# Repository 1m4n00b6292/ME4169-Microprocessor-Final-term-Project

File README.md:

# ME4169 Microprocessor Final term project

This is the final term project of ME4169 - Microprocessor course conducted by HUST

## Overview

**ME4169 Microprocessor Final term project**, aka, **VIXULY** is a closed-loop DC motor speed controller built around an **ATmega88PA** running at 16 MHz. The motor speed is measured by a quadrature encoder and regulated by a fixed-point PID controller. The target speed can be set either by a **potentiometer** or by commands sent over **UART**. A small **WeAct ST7735 TFT module** shows the current mode, the system state, the target speed and the measured speed (RPM).

The firmware is written as bare-metal AVR code (direct register access, hand-written ISRs). The Arduino framework is only used for `millis()` and the `setup()`/`loop()` entry points, under PlatformIO.

<!-- Fixed width, centered -->
<p align="center">
  
  <br>
  <em>Figure 1: PCB 3D view (top)</em>
</p>

## Main Components

### Hardware

| Part | Function |
|------|----------|
| ATmega88PA-A (TQFP-32) + 16 MHz crystal | Main MCU |
| DRV8220 | Brushed DC motor driver (H-bridge) |
| Quadrature encoder | Speed feedback (x4 decoding) |
| [WeAct ST7735 TFT module](https://github.com/WeActStudio/WeAct-ST7735) (128x160) | Status display, SPI |
| TXB0106 | Level shifter between the 5 V MCU and the 3.3 V TFT |
| Potentiometer (RV1) | Manual speed setpoint |
| 2 push buttons + 2 LEDs | RUN / STOP user interface |
| LMR51420 buck + AP2112K-3.3 LDO | 12 V input to 5 V and 3.3 V rails |
| PFET + Zener input stage | Reverse polarity protection |
### Pin Map

| Signal | Pin | Notes |
|--------|-----|-------|
| TFT RST / BL / CS | PB0 / PB1 / PB2 | |
| TFT MOSI / SCK | PB3 / PB5 | Hardware SPI |
| TFT DC | PD7 | |
| Encoder A / B | PD2 / PD3 | INT0 / INT1 |
| Motor nSLEEP | PD4 | |
| Motor IN1/PH, IN2/EN | PD5 / PD6 | Software PWM on Timer2 |
| UART RX | PD0 | RX only |
| Potentiometer | PC0 | ADC0 |
| RUN button / RUN LED | PC1 / PC2 | |
| STOP button / STOP LED | PC3 / PC4 | |

> **JP1** on the board selects the DRV8220 control mode. Keep it **open** for PWM (IN1/IN2) mode (default). If it is soldered, enable `MOTOR_MODE_PH_EN` in `config.h`.

<!-- Fixed width, centered -->
<p align="center">
  
  <br>
  <em>Figure 2: Layout view (top)</em>
</p>

### Software Modules

| File | Description |
|------|-------------|
| `main.cpp` | Entry point: only calls `app_init()` and `app_update()` |
| `app.cpp / app.h` | Application layer: state machine, mode selection, LEDs, display updates (implements `VIXULY_Logic.txt`) |
| `config.h` | **Single place for every tunable value**: pins, TFT, ADC, encoder, motor, PID gains, button timing, UI layout |
| `motion.c / motion.h` | Fixed-point (Q8) PID velocity controller with feed-forward, setpoint ramp, anti-windup and filtered D-term |
| `motor.c / motor.h` | DRV8220 driver, software PWM on Timer2 ISRs (Timer0 / `millis()` untouched) |
| `encoder_mini.cpp / .h` | x4 quadrature decoder, optional STM32-style digital input filter (Timer1), velocity and RPM calculation |
| `button.c / button.h` | Debounced button with short-press / long-press detection |
| `uart.c / uart.h` | Interrupt-driven UART receiver with ring buffer and ASCII integer parser |
| `adc.c / adc.h` | Minimal 10-bit ADC driver |
| `st7735_mini.c / .h` | Lightweight text-only driver for the WeAct ST7735 module (small flash footprint) |

## Operation Logic

The system has three user-visible states: **STOP**, **RUN** and **SELECT** (mode selection). There are two operation modes:

- **POTENTIOMETER**: the speed setpoint comes from the pot on PC0
- **UART**: the speed setpoint comes from serial commands

| Button | Current state | Action | Result |
|--------|---------------|--------|--------|
| STOP | any | Press | Stop the system. The motor driver is put to sleep (PD4 low), the PID is reset, and any unfinished mode selection is cancelled |
| RUN | STOP | Short press | Start running in the current mode |
| RUN | STOP | Hold ~2 s | Enter mode selection |
| RUN | SELECT | Short press | Swap between POTENTIOMETER and UART |
| RUN | SELECT | Hold ~2 s | Confirm the shown mode and return to STOP |
| RUN | RUN | any | Ignored |

**LEDs**

- RUN LED (PC2) is on only while the system is running
- STOP LED (PC4) is on while stopped or selecting

The global variable `running` is `1` while the system is running and `0` otherwise.

## Quick User Guide

### 1. Build and flash

The project uses [PlatformIO](https://platformio.org/).

1. Clone the repository:
   ```bash
   git clone https://github.com/1m4n00b6292/VIXULY-Source-code.git
   ```
2. Open the `Department of Software Engineering` folder in VS Code with the PlatformIO extension.
3. Review `src/config.h`, especially the items in the **Configuration** section below.
4. Build and upload with your ISP programmer, using the debug/programming header on the board.

### 2. Power up

1. Connect a **12 V DC** supply to the input terminal (observe polarity).
2. Connect the motor and the encoder.
3. After power-up the system starts in **STOP** (red "STOP" on the screen, STOP LED on).

### 3. Select a mode

1. In STOP, hold the **RUN** button for about 2 s. The screen shows **SELECT** in orange.
2. Short-press **RUN** to toggle between `Mode: Potentiometer` and `Mode: UART`.
3. Hold **RUN** for about 2 s again to confirm. The system returns to STOP with the chosen mode.

### 4. Run

Short-press **RUN**. The screen shows green **RUNNING**, and the RUN LED turns on.

- **Potentiometer mode**: turn the pot. The center position (with a small dead band) is 0 RPM. Turning it to one side gives clockwise rotation, and turning it to the other side gives counter-clockwise rotation. Full travel corresponds to `APP_MAX_RPM`.
- **UART mode**: send speed commands as described below.

Press **STOP** at any time to stop the motor.

### 5. UART protocol

| Setting | Value |
|---------|-------|
| Baud rate | 115200 |
| Format | 8N1 |
| Direction | RX only (PC to board) |

Send one **signed integer per line**, ending with `\n` or `\r`. The value is clamped to **-255 ... +255** and scaled linearly to **-APP_MAX_RPM ... +APP_MAX_RPM**. Other characters are ignored.

```text
255\n     -> full speed, forward
-128\n    -> about half speed, reverse
0\n       -> stop (motor held at 0 RPM)
```

Example with Python:

```python
import serial
ser = serial.Serial("COM3", 115200)
ser.write(b"200\n")
```

### 6. Display

```text
Mode: Potentiometer        <- active mode
Velocity =                 <- measured speed
 1234 (RPM)
Target = 1500              <- setpoint
RUNNING                    <- state
```

## Configuration

All the important parameters are in `config.h`:

| Parameter | Meaning |
|-----------|---------|
| `ENC_PPR` | **Set this to your encoder's pulses per revolution.** The RPM calculation depends on it |
| `ENC_INVERT` | Swap the encoder counting direction |
| `ENC_FILTER_N`, `ENC_FILTER_SAMPLE_HZ` | Encoder input noise filter (set `ENC_FILTER_N` to 1 to disable) |
| `MOTOR_INVERT` | Flip the motor rotation direction |
| `MOTOR_T2_PRESCALER` | Software PWM frequency (default 32 gives about 1.95 kHz) |
| `MOTION_KP`, `MOTION_KI`, `MOTION_KD`, `MOTION_KFF` | PID and feed-forward gains, **tune these on your motor** |
| `MOTION_ACCEL` | Setpoint ramp rate in units/s (0 = off) |
| `APP_MAX_RPM` | Speed at full pot travel or UART ±255 |
| `APP_OPEN_LOOP` | `1` = send the target directly as PWM duty (no PID), useful for testing the hardware |
| `APP_POT_INVERT`, `APP_POT_DEADBAND` | Potentiometer direction and dead band |
| `BTN_LONG_MS`, `BTN_DEBOUNCE_MS` | Button timing |
| `TFT_LANDSCAPE`, `TFT_COL_OFFSET`, `TFT_ROW_OFFSET` | Display orientation and offsets |

> **Tip:** if something does not behave as expected during bring-up, set `APP_OPEN_LOOP` to `1` first to check the motor and the pot without the PID in the way, then switch back to closed-loop and tune the gains.

## Repository Structure

The repository is organized like a university, with one "department" per area of the project:

```text
VIXULY-Source-code/
├── Department of Administration Services/     # Administration: final term report
│   └── (final term report)
│
├── Department of Electrical Engineering/      # Electrical: PCB design files
│   ├── Docs/                                  #   Datasheets, Reference designs,... used in this project
│   ├── Util/                                  #   External libraries, 3D CAD files used in the PCB design
│   └── 中国制造的PCB/                          #   PCB project, Schematic, Layout, Gerber files,..
│
├── Department of Mechanical Engineering/      # Mechanical: 3D printed parts
│   └── Encoder flange/                        #   Flange with a radial magnet at the center,
│                                              #   for a second encoder used to cross-check
│                                              #   the velocity measurement
│
├── Department of Software Engineering/        # Software: the firmware
│   ├── src/
│   │   ├── main.cpp
│   │   ├── app.cpp / app.h
│   │   ├── config.h
│   │   ├── motion.c / motion.h
│   │   ├── motor.c / motor.h
│   │   ├── encoder_mini.cpp / encoder_mini.h
│   │   ├── button.c / button.h
│   │   ├── uart.c / uart.h
│   │   ├── adc.c / adc.h
│   │   └── st7735_mini.c / st7735_mini.h
│   ├── VIXULY_Logic.txt                       #   Button / mode logic specification
│   └── platformio.ini
│
└── README.md
```

| Folder | Contents |
|--------|----------|
| **Department of Administration Services** | Final term report |
| **Department of Electrical Engineering** | Schematic, PCB files and Gerber files of the VI XU LY board |
| **Department of Mechanical Engineering** | 3D printed parts. Currently a flange with a radial magnet at its center, used for a second encoder that confirms the velocity measurement |
| **Department of Software Engineering** | Firmware for the ATmega88PA (this is what the sections above describe) |

> **Build note:** open the `Department of Software Engineering` folder (not the repo root) in PlatformIO.
## Acknowledgements

- Display module: [WeAct Studio ST7735](https://github.com/WeActStudio/WeAct-ST7735). `st7735_mini` is a trimmed, text-only driver written for this project so that it fits in the ATmega88PA's flash.

## Course Information

- **Course:** ME4169 - Microprocessor
- **University:** Hanoi University of Science and Technology (HUST)
- **Type:** Final term project

## Authors

| Member | GitHub | Role |
|--------|--------|------|
| **1m4n00b** | [@1m4n00b6292](https://github.com/1m4n00b6292) | Hardware and system design: PCB design, schematic, component selection, planning the system function and logic |
| **depzaineversai** | [@anhkiethp58-hue](https://github.com/anhkiethp58-hue) | Firmware: firmware development and integration |

## License

This project is licensed under the [MIT License](LICENSE).

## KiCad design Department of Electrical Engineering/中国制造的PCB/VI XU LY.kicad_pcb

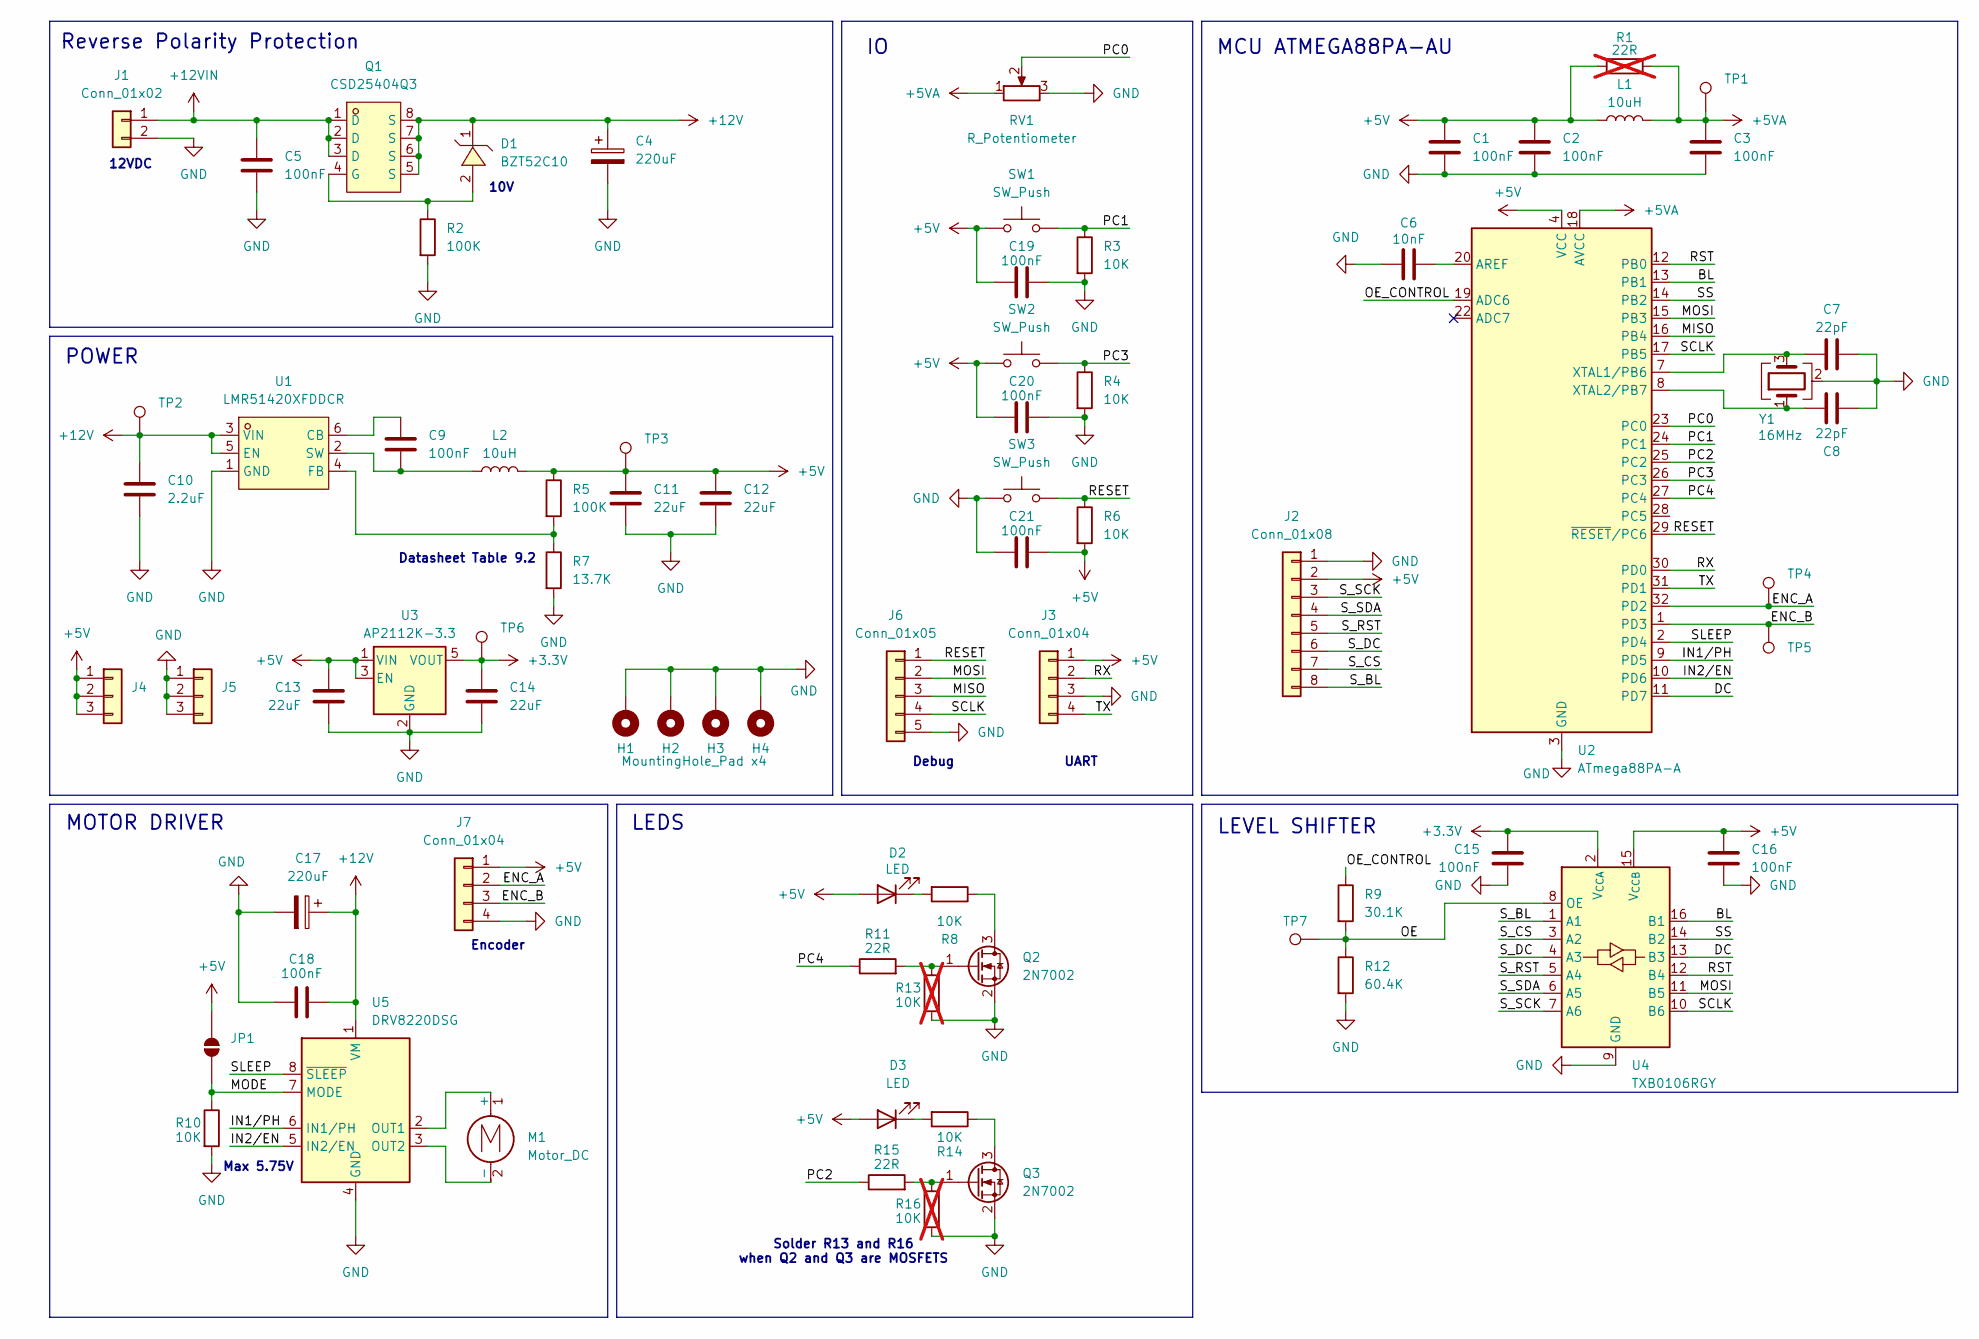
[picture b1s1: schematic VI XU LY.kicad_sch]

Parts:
C1, C2, C3, C9, C15, C16, C18, C19, C20, C21: 100nF; C_0603_1608Metric_Pad1.08x0.95mm_HandSolder
C4, C17: 220uF; CP_Elec_6.3x7.7
C5: 100nF; C_0805_2012Metric_Pad1.18x1.45mm_HandSolder
C6: 10nF; C_0603_1608Metric_Pad1.08x0.95mm_HandSolder
C7, C8: 22pF; C_0603_1608Metric_Pad1.08x0.95mm_HandSolder
C10: 2.2uF; C_0603_1608Metric_Pad1.08x0.95mm_HandSolder
C11, C12, C13, C14: 22uF; C_1206_3216Metric_Pad1.33x1.80mm_HandSolder
D1: BZT52C10; SOD-123_L2.8-W1.8-LS3.7-RD; MPN BZT52C10; LCSC Part C173431
D2, D3: LED; LED_1206_3216Metric_Pad1.42x1.75mm_HandSolder
H1, H2, H3: MountingHole_Pad; MountingHole_3.2mm_M3_Pad_TopBottom
H4: MountingHole_Pad x4; MountingHole_3.2mm_M3_Pad_TopBottom
J1: Conn_01x02; TerminalBlock_Phoenix_MKDS-1,5-2-5.08_1x02_P5.08mm_Horizont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
J2: Conn_01x08; PinSocket_1x08_P2.54mm_Vertical
J3, J7: Conn_01x04; JST_XH_S4B-XH-A-1_1x04_P2.50mm_Horizontal
J4, J5: Conn_01x03; PinHeader_1x03_P2.54mm_Vertical
J6: Conn_01x05; JST_XH_S5B-XH-A-1_1x05_P2.50mm_Horizontal
JP1: SolderJumper_2_Open; SolderJumper-2_P1.3mm_Open_TrianglePad1.0x1.5mm
L1: 10uH; L_0603_1608Metric_Pad1.05x0.95mm_HandSolder
L2: 10uH; L_Vishay_IHLP-1616
M1: Motor_DC; TerminalBlock_Phoenix_MKDS-1,5-2-5.08_1x02_P5.08mm_Horizont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
Q1: CSD25404Q3; VSON-CLIP-8_L3.3-W3.3-P0.65-BL; MPN CSD25404Q3; LCSC Part C2865523
Q2, Q3: 2N7002; SOT-23
R1: 22R; R_0603_1608Metric_Pad0.98x0.95mm_HandSolder; not fitted
R2, R5: 100K; R_0603_1608Metric_Pad0.98x0.95mm_HandSolder
R3, R4, R6, R8, R10, R14: 10K; R_0603_1608Metric_Pad0.98x0.95mm_HandSolder
R7: 13.7K; R_0603_1608Metric_Pad0.98x0.95mm_HandSolder
R9: 30.1K; R_0603_1608Metric_Pad0.98x0.95mm_HandSolder
R11, R15: 22R; R_0603_1608Metric_Pad0.98x0.95mm_HandSolder
R12: 60.4K; R_0603_1608Metric_Pad0.98x0.95mm_HandSolder
R13, R16: 10K; R_0603_1608Metric_Pad0.98x0.95mm_HandSolder; not fitted
RV1: R_Potentiometer; Potentiometer_Alps_RK097_Dual_Horizontal
SW1, SW2, SW3: SW_Push; SW_SPST_Omron_B3F-315x_Angled
TP1, TP2, TP3, TP4, TP5, TP6, TP7: TestPoint; TestPoint_Pad_D1.0mm
U1: LMR51420XFDDCR; SOT-23-6_L2.9-W1.6-P0.95-LS2.8-BL; MPN LMR51420XFDDCR; LCSC Part C5752071
U2: ATmega88PA-A; TQFP-32_7x7mm_P0.8mm
U3: AP2112K-3.3; SOT-23-5
U4: TXB0106RGY; Texas_RGY_R-PVQFN-N16_EP2.05x2.55mm
U5: DRV8220DSG; WSON-8-1EP_2x2mm_P0.5mm_EP0.9x1.6mm
Y1: 16MHz; Crystal_SMD_3225-4Pin_3.2x2.5mm

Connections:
+3.3V: C14.1, C15.1, TP6.1 (1_1), U3.5 (VOUT), U4.2 (V_{CCA})
+5V: C1.1, C2.1, C11.1, C12.1, C13.1, C16.1, C19.1, C20.1, C21.2, D2.2 (A), D3.2 (A), J2.2, J3.1, J4.1, J4.2, J4.3, J7.1, JP1.2 (B), L1.1, L2.2, R1.1, R5.1, R6.2, SW1.1, SW2.1, TP3.1 (1_1), U2.4 (VCC), U2.6 (VCC), U3.1 (VIN), U3.3 (EN), U4.15 (V_{CCB})
+5VA: C3.1, L1.2, R1.2, RV1.1, TP1.1 (1_1), U2.18 (AVCC)
+12V: C4.1, C10.1, C17.1, C18.2, D1.1, Q1.5 (S), Q1.6 (S), Q1.7 (S), Q1.8 (S), TP2.1 (1_1), U1.3 (VIN), U1.5 (EN), U5.1 (VM)
+12VIN: C5.1, J1.1, Q1.1 (D), Q1.2 (D), Q1.3 (D)
/BL: U2.13 (PB1), U4.16 (B1)
/DC: U2.11 (PD7), U4.13 (B3)
/ENC_A: J7.2, TP4.1 (1_1), U2.32 (PD2)
/ENC_B: J7.3, TP5.1 (1_1), U2.1 (PD3)
/IN1/PH: U2.9 (PD5), U5.6 (IN1/PH)
/IN2/EN: U2.10 (PD6), U5.5 (IN2/EN)
/MISO: J6.3, U2.16 (PB4)
/MODE: JP1.1 (A), R10.1, U5.7 (MODE)
/MOSI: J6.2, U2.15 (PB3), U4.11 (B5)
/OE: R9.2, R12.1, TP7.1 (1_1), U4.8 (OE)
/OE_CONTROL: R9.1, U2.19 (ADC6)
/PC0: RV1.2, U2.23 (PC0)
/PC1: R3.1, SW1.2, U2.24 (PC1)
/PC2: R15.1, U2.25 (PC2)
/PC3: R4.1, SW2.2, U2.26 (PC3)
/PC4: R11.1, U2.27 (PC4)
/RESET: J6.1, R6.1, SW3.2, U2.29 (~RESET/PC6)
/RST: U2.12 (PB0), U4.12 (B4)
/RX: J3.2, U2.30 (PD0)
/SCLK: J6.4, U2.17 (PB5), U4.10 (B6)
/SLEEP: U2.2 (PD4), U5.8 (~SLEEP)
/SS: U2.14 (PB2), U4.14 (B2)
/S_BL: J2.8, U4.1 (A1)
/S_CS: J2.7, U4.3 (A2)
/S_DC: J2.6, U4.4 (A3)
/S_RST: J2.5, U4.5 (A4)
/S_SCK: J2.3, U4.7 (A6)
/S_SDA: J2.4, U4.6 (A5)
/TX: J3.4, U2.31 (PD1)
GND: C1.2, C2.2, C3.2, C4.2, C5.2, C6.2, C7.2, C8.2, C10.2, C11.2, C12.2, C13.2, C14.2, C15.2, C16.2, C17.2, C18.1, C19.2, C20.2, C21.1, H1.1 (1_1), H2.1 (1_1), H3.1 (1_1), H4.1 (1_1), J1.2, J2.1, J3.3, J5.1, J5.2, J5.3, J6.5, J7.4, Q2.2 (S), Q3.2 (S), R2.2, R3.2, R4.2, R7.2, R10.2, R12.2, R13.2, R16.2, RV1.3, SW3.1, U1.1 (GND), U2.3 (GND), U2.5 (GND), U2.21 (GND), U3.2 (GND), U4.9 (GND), U4.17 (GND), U5.4 (GND), U5.9 (GND), Y1.2 (G), Y1.4 (G)
unnamed: D2.1 (K), R8.2
unnamed: D3.1 (K), R14.2
unnamed: M1.1 (+), U5.2 (OUT1)
unnamed: M1.2 (-), U5.3 (OUT2)
unnamed: D1.2, Q1.4 (G), R2.1
unnamed: Q2.3 (D), R8.1
unnamed: Q2.1 (G), R11.2, R13.1
unnamed: Q3.3 (D), R14.1
unnamed: Q3.1 (G), R15.2, R16.1
unnamed: C9.1, U1.6 (CB)
unnamed: R5.2, R7.1, U1.4 (FB)
unnamed: C9.2, L2.1, U1.2 (SW)
unnamed: C6.1, U2.20 (AREF)
unnamed: C7.1, U2.7 (XTAL1/PB6), Y1.3
unnamed: C8.1, U2.8 (XTAL2/PB7), Y1.1

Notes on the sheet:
Datasheet Table 9.2
UART
12VDC
POWER
LEVEL SHIFTER
Reverse Polarity Protection
LEDS
10V
Solder R13 and R16 when Q2 and Q3 are MOSFETS
MOTOR DRIVER
Debug
MCU ATMEGA88PA-AU
Encoder
Max 5.75V

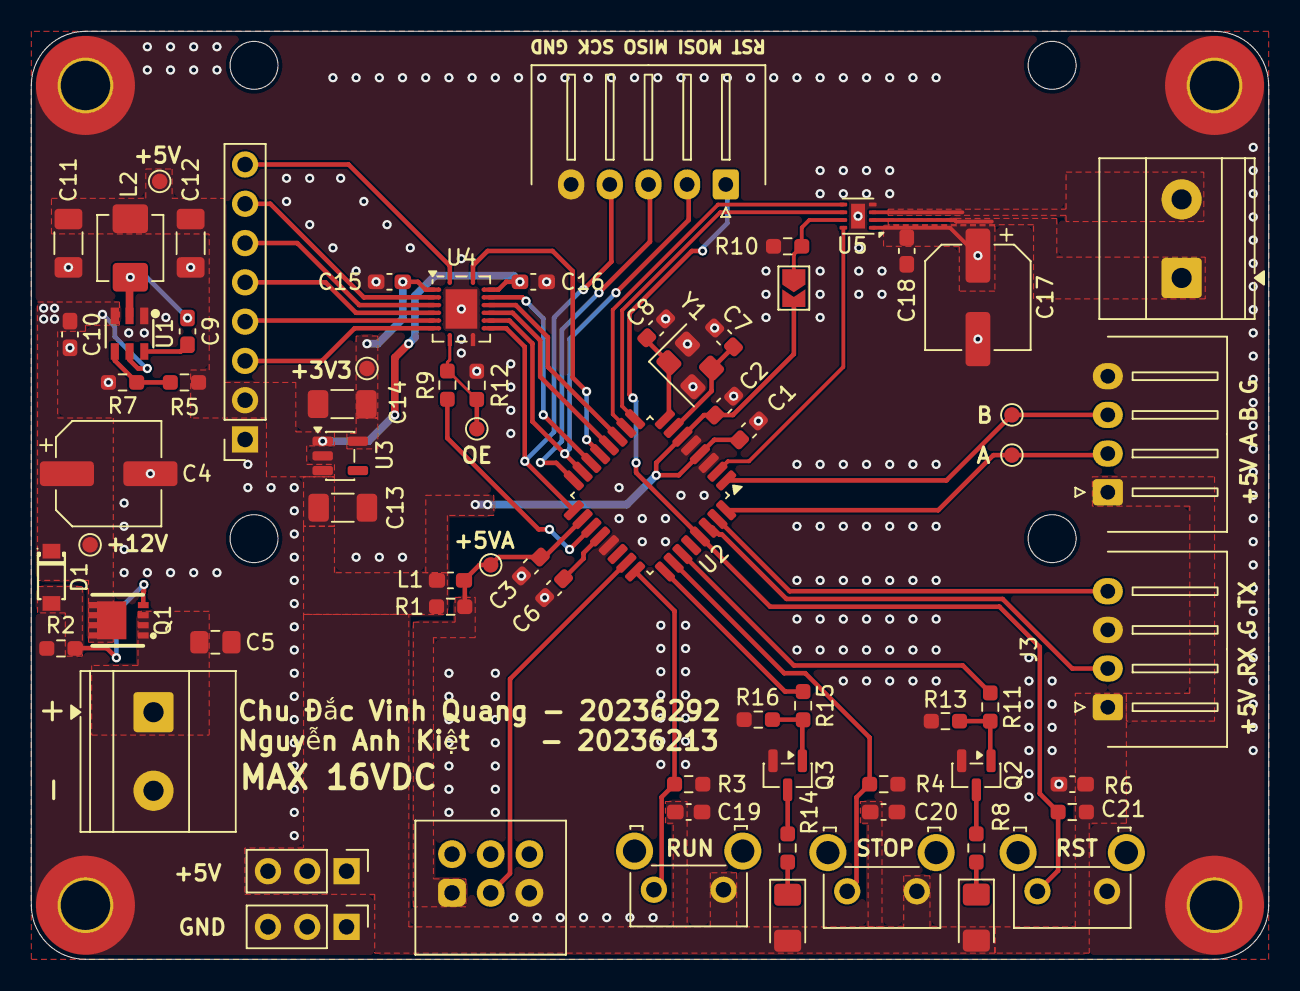
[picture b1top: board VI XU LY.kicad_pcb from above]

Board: 2 copper layers, 80.0 x 60.0 mm, 75 parts (0 on the bottom side), 50 nets.

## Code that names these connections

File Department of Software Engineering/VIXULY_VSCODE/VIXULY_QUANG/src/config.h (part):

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/* ======================================================================
 * 2. PIN MAP
 *
 *   PB0 TFT_RST    PB1 TFT_BL     PB2 TFT_CS     PB3 TFT_MOSI(fixed)  PB5 TFT_SCK(fixed)
 *   PD7 TFT_DC
 *   PD2 ENC_A (INT0, fixed)       PD3 ENC_B (INT1, fixed)
 *   PD4 MOTOR_SLEEP   PD5 MOTOR_IN1/PH (Timer2 COMPA)   PD6 MOTOR_IN2/EN (Timer2 COMPB)
 *   PC0 POT (ADC0)
 *
 * Ports are fixed in the code (PORTB / PORTD); only the bit numbers are
 * configurable. Pins marked "fixed" or tied to a Timer2/INT vector cannot move
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 * ====================================================================== */

/* ---- TFT (PORTB, DC on PORTD) ---- */
#define TFT_RST_PIN     PB0
#define TFT_BL_PIN      PB1
#define TFT_CS_PIN      PB2
#define TFT_MOSI_PIN    PB3         /* fixed by hardware SPI */
#define TFT_SCK_PIN     PB5         /* fixed by hardware SPI */
#define TFT_DC_PIN      PD7         /* PORTD */

/* ---- Encoder (PORTD) - tied to INT0 / INT1 ---- */
#define ENC_A_BIT       2
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/* ======================================================================
 * 4. ADC  (adc)
 * ====================================================================== */
#define ADC_POT_CHANNEL     0       /* PC0 / ADC0 */

/* Reference: 0 = AREF, 1 = AVCC (+5VA via L1/C), 2 = internal 1.1 V */
#define ADC_REFERENCE       1
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
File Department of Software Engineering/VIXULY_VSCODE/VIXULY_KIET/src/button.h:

/*
 * ATmega88PA - nut nhan va LED, lap trinh thanh ghi.
 * PC1 = RUN, PC3 = STOP: nhan HIGH, nha LOW (R3/R4 keo xuong ngoai).
 * PC2 = LED RUN, PC4 = LED STOP: sang HIGH. PD4 = nSLEEP qua motor.c.
 * Theo VIXULY_Logic: running = 1 la STOP, running = 0 la RUN.
 *
 * Goi motor_init() / motion_init() truoc button_init(), sau do bat ngat
 * (sei() neu bare-metal). Goi button_update() lien tuc trong loop,
 * nen cach nhau <= 5 ms; khong dung delay(250) trong main cu.
 * Chi goi cac API tu chuong trinh chinh, KHONG goi tu ISR.
 *
 * Thu vien so huu Timer1 / TIMER1_COMPA_vect: CTC, tick 1 ms.
 * ISR chi dem thoi gian; xu ly nut va motor_enable() o chuong trinh chinh.
 * Khong dung Arduino API; khong doi Timer0, Timer2, UART hay ngat encoder.
 * COM1A/B = 0 nen PB1/PB2 van dung duoc cho TFT.
 * Khong tat ngat >= 1 ms; khong dung thu vien khac chiem Timer1.
 *
 * Khoi dong STOP/POT. Phai nha ca hai nut truoc khi nhan RUN.
 * RUN ngan duoc xu ly khi nha; RUN giu 2 s chi phat mot su kien.
 * Trong menu: RUN ngan doi lua chon, RUN giu 2 s xac nhan.
 * STOP duoc xu ly ngay khi nhan on dinh 20 ms, huy menu va uu tien RUN.
 * Sau STOP phai nha ca hai nut roi moi nhan RUN lai.
 * LED chi bao trang thai chay/dung, khong nhap nhay khi chon che do.
 *
 * Khong goi motor_set(), motor_brake(), motion_update() khi STOP:
 * cac ham nay co the danh thuc driver. Khi dung PID, goi motion_stop()
 * khi chuyen sang STOP de reset PID va giu PD4 LOW.
 * Chi doc bien running, khong gan tu main va khong khai bao trung ten.
 */
#ifndef BUTTON_H
#define BUTTON_H

#include <stdint.h>

/* Neu thay doi, dat build flags cho ca button.cpp va chuong trinh chinh. */
#ifndef BUTTON_DEBOUNCE_MS
#define BUTTON_DEBOUNCE_MS 20UL
#endif
#ifndef BUTTON_LONG_PRESS_MS
#define BUTTON_LONG_PRESS_MS 2000UL
#endif

/* Mac dinh dung khi vao menu; xac nhan xong van STOP, nhan RUN de chay.
 * Dat bang 0 neu muon giu trang thai RUN/STOP trong luc chon che do.
 */
#ifndef BUTTON_STOP_ON_SELECT
#define BUTTON_STOP_ON_SELECT 1
#endif

#define BUTTON_STOPPED   1U
#define BUTTON_RUNNING   0U
#define BUTTON_MODE_POT  0U
#define BUTTON_MODE_UART 1U

#ifdef __cplusplus
extern "C" {
#endif

extern uint8_t running;

void button_init(void);
void button_update(void);

/* Dung motor, huy lua chon chua xac nhan, cho nha ca hai nut. */
void button_stop(void);

/* Che do da xac nhan dung de chon nguon toc do PC0 / UART. */
uint8_t button_get_mode(void);
/* Che do tam thoi trong menu, chi dung de hien thi. */
uint8_t button_get_selected_mode(void);
uint8_t button_is_selecting(void);

#ifdef __cplusplus
}
#endif
#endif /* BUTTON_H */
